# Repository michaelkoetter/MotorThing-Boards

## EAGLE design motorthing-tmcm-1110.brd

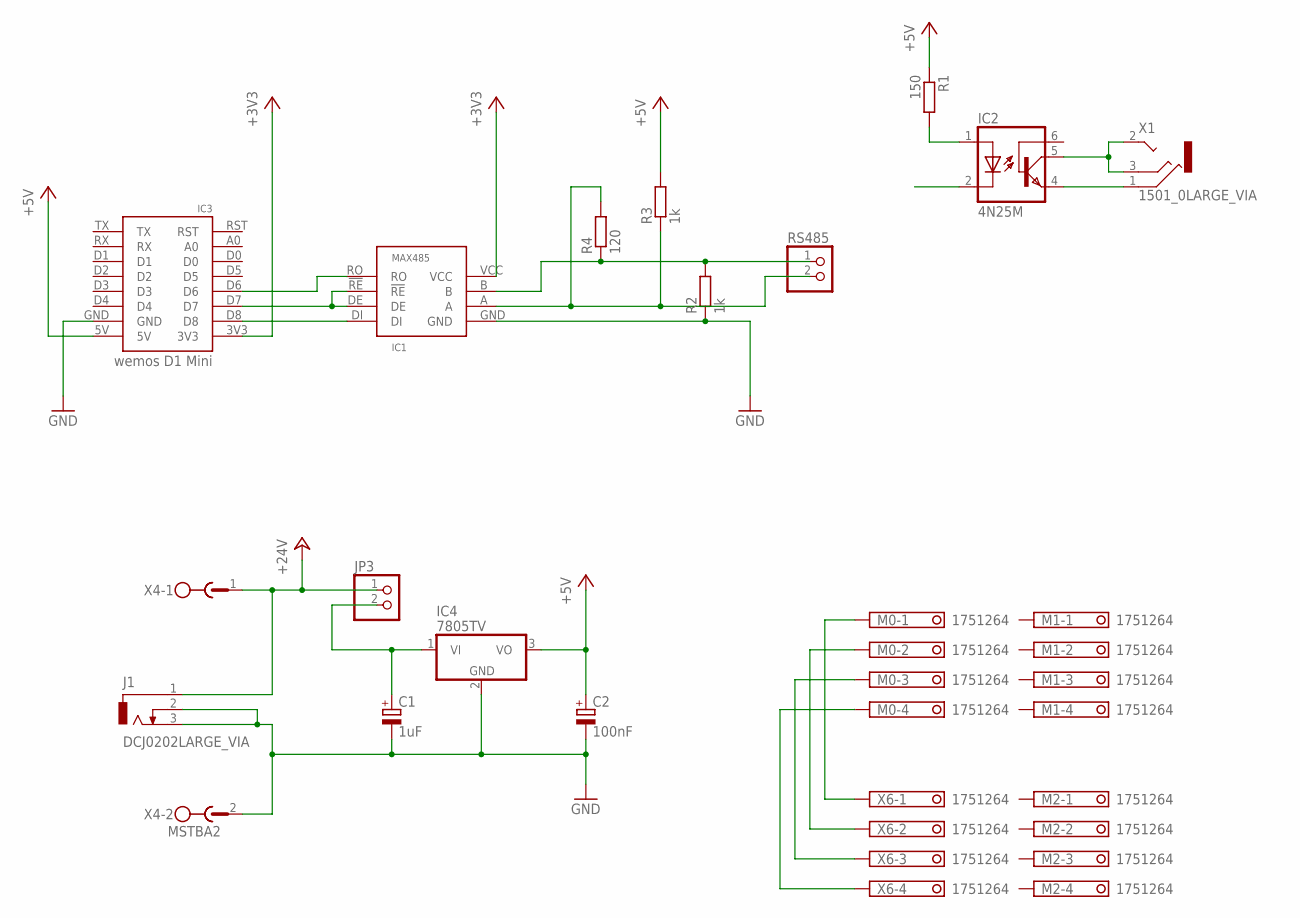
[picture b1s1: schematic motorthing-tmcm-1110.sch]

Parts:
C1: 1uF; TT2D6
C2: 100nF; TT2D5
IC1: MAX485; DIL08
IC2: 4N25M; DIL06
IC3: wemos D1 Mini; WEMOS-NOSILK
IC4: 7805TV; TO220V
J1: DCJ0202LARGE_VIA; DCJ0202_LV
JP3: PINHD-1X2; 1X02
M0, M1, M2: 1751264
R1: 150; 0207/10
R2, R3: 1k; 0207/10
R4: 120; 0207/10
RS485: PINHD-1X2; 1X02
X1: 1501_0LARGE_VIA; 1501_05_LV
X4: MSTBA2
X6: 1751264

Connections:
+3V3: IC1.VCC, IC3.3V3
+5V: C2.+, IC3.5V, IC4.3 (VO), R1.1, R3.2
+24V: J1.1, JP3.1, X4.1
GND: C1.-, C2.-, IC1.GND, IC3.GND, IC4.2 (GND), J1.2, J1.3, R2.1, X4.2
unnamed: IC2.1 (A), R1.2
unnamed: IC2.4 (EMI), X1.1
unnamed: IC1.RO, IC3.D6
unnamed: IC1.DI, IC3.D8
unnamed: M0.1, X6.1
unnamed: IC2.5 (COL), X1.2, X1.3
unnamed: M0.2, X6.2
unnamed: M0.3, X6.3
unnamed: IC1.!RE, IC1.DE, IC3.D7
unnamed: M0.4, X6.4
unnamed: C1.+, IC4.1 (VI), JP3.2
RS485+: IC1.A, R3.1, R4.2, RS485.2
RS485-: IC1.B, R2.2, R4.1, RS485.1

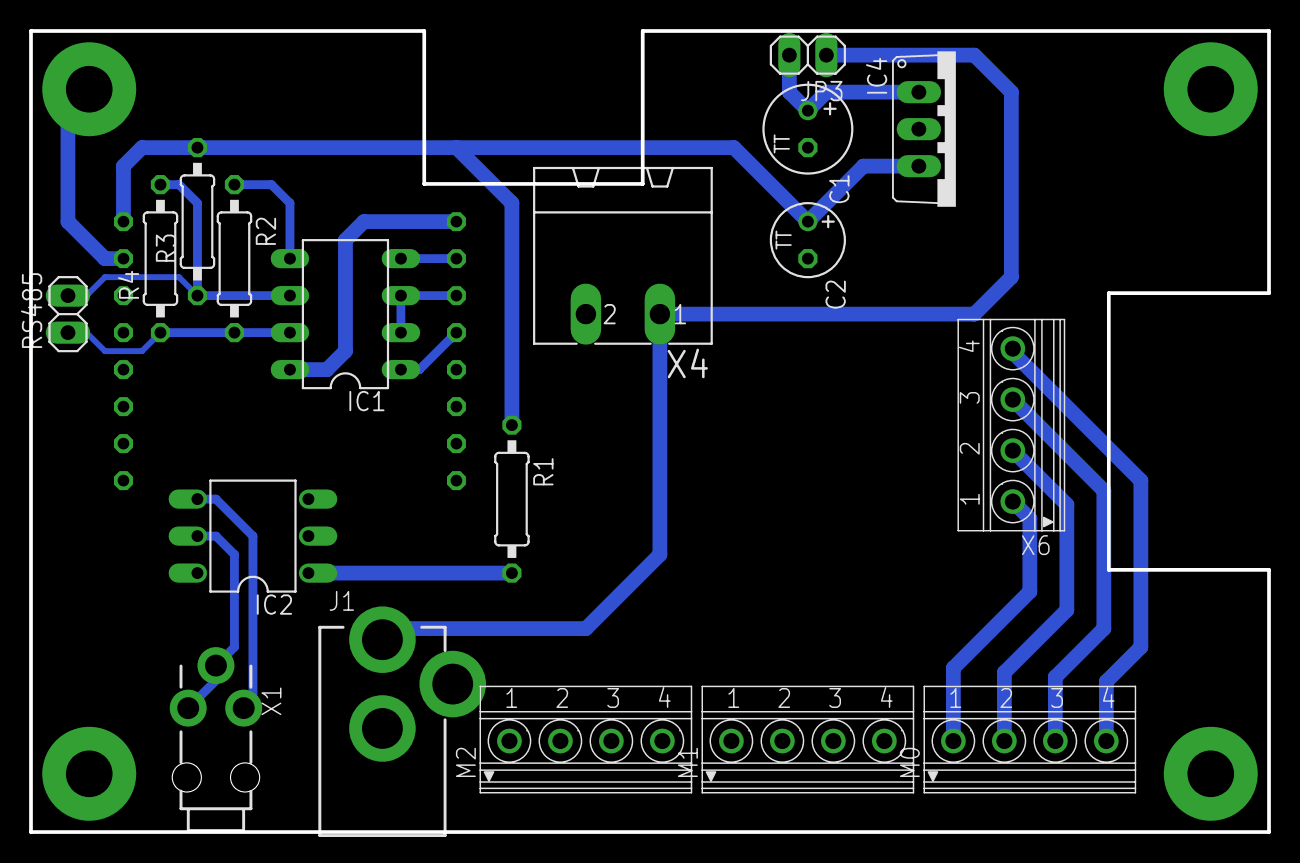
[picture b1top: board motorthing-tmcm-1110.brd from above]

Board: 2 copper layers, 85.0 x 55.0 mm, 19 parts (0 on the bottom side), 17 nets.

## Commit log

2016-04-05 :circus_tent: Added .gitattributes
2016-04-05 v2 prototype for TMCM-110
2016-04-05 fix resistor values
2016-04-05 start working on TMCM-1110 layout
2016-04-08 board outline
